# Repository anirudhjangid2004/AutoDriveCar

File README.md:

# AutoDriveCar
EDL 2025 project

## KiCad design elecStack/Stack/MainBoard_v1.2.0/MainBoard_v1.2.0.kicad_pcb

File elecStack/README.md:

### Electrical Architecture Information

The repo will contain the following

- Electrical board design
- Code for the low level microcontroller

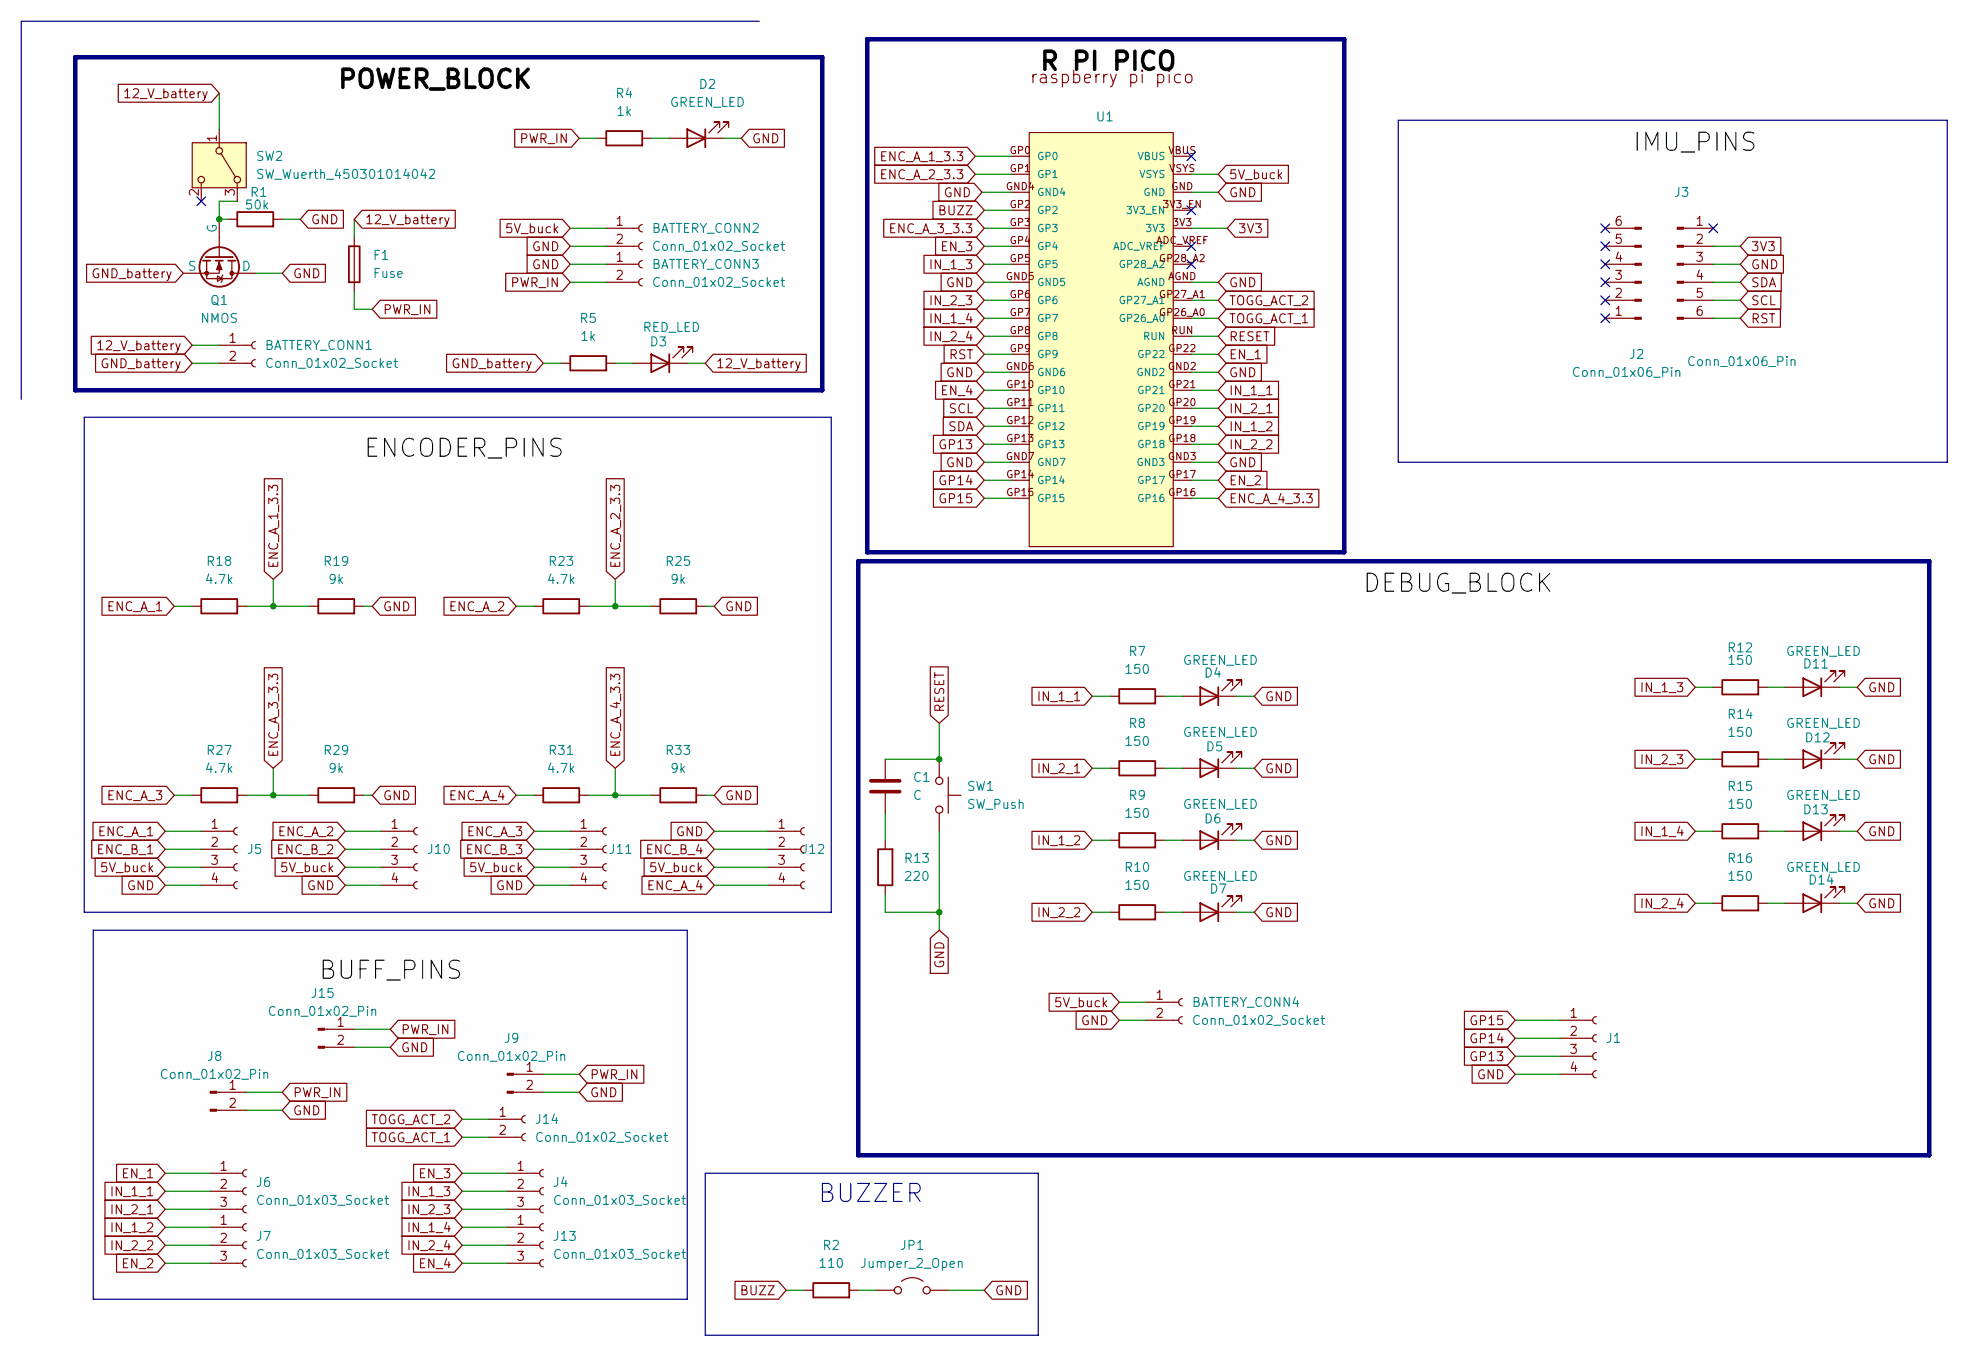
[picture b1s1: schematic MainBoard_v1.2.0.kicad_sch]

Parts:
BATTERY_CONN1, BATTERY_CONN2, BATTERY_CONN3, BATTERY_CONN4: Conn_01x02_Socket; TerminalBlock_Phoenix_MKDS-1,5-2-5.08_1x02_P5.08mm_Horizont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
C1: C; C_1210_3225Metric_Pad1.33x2.70mm_HandSolder
D2, D4, D5, D6, D7, D11, D12, D13, D14: GREEN_LED; LED_0805_2012Metric_Pad1.15x1.40mm_HandSolder
D3: RED_LED; LED_0805_2012Metric_Pad1.15x1.40mm_HandSolder
F1: Fuse; Fuse_Blade_Mini_directSolder
J1, J5, J10, J11, J12: Conn_01x04_Socket; JST_XH_B4B-XH-A_1x04_P2.50mm_Vertical
J2, J3: Conn_01x06_Pin; PinHeader_1x06_P2.54mm_Vertical
J4, J6, J7, J13: Conn_01x03_Socket; JST_XH_B3B-XH-A_1x03_P2.50mm_Vertical
J8, J9, J15: Conn_01x02_Pin; TerminalBlock_Phoenix_MKDS-1,5-2-5.08_1x02_P5.08mm_Horizont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
J14: Conn_01x02_Socket; JST_XH_B2B-XH-A_1x02_P2.50mm_Vertical
JP1: Jumper_2_Open; Buzzer_12x9.5RM7.6
Q1: NMOS; IRF540N
R1: 50k; R_0805_2012Metric_Pad1.20x1.40mm_HandSolder
R2: 110; R_0805_2012Metric_Pad1.20x1.40mm_HandSolder
R4, R5: 1k; R_0805_2012Metric_Pad1.20x1.40mm_HandSolder
R7, R8, R9, R10, R12, R14, R15, R16: 150; R_0805_2012Metric_Pad1.20x1.40mm_HandSolder
R13: 220; R_0805_2012Metric_Pad1.20x1.40mm_HandSolder
R18, R23, R27, R31: 4.7k; R_0805_2012Metric_Pad1.20x1.40mm_HandSolder
R19, R25, R29, R33: 9k; R_0805_2012Metric_Pad1.20x1.40mm_HandSolder
SW1: SW_Push; SW_PUSH_6mm_H5mm
SW2: SW_Wuerth_450301014042; SW_Slide-03_Wuerth-WS-SLTV_10x2.5x6.4_P2.54mm
U1: RASPBERRY_PI_PICO

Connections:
3V3: J3.2, U1.3V3
5V_buck: BATTERY_CONN2.1, BATTERY_CONN4.1, J5.3, J10.3, J11.3, J12.3, U1.VSYS
12_V_battery: BATTERY_CONN1.1, D3.1 (K), F1.1, SW2.1 (B)
BUZZ: R2.1, U1.GP2
ENC_A_1: J5.1, R18.1
ENC_A_1_3.3: R18.2, R19.1, U1.GP0
ENC_A_2: J10.1, R23.1
ENC_A_2_3.3: R23.2, R25.1, U1.GP1
ENC_A_3: J11.1, R27.1
ENC_A_3_3.3: R27.2, R29.1, U1.GP3
ENC_A_4: J12.4, R31.1
ENC_A_4_3.3: R31.2, R33.1, U1.GP16
ENC_B_1: J5.2
ENC_B_2: J10.2
ENC_B_3: J11.2
ENC_B_4: J12.2
EN_1: J6.1, U1.GP22
EN_2: J7.3, U1.GP17
EN_3: J4.1, U1.GP4
EN_4: J13.3, U1.GP10
GND: BATTERY_CONN2.2, BATTERY_CONN3.1, BATTERY_CONN4.2, D2.1 (K), D4.1 (K), D5.1 (K), D6.1 (K), D7.1 (K), D11.1 (K), D12.1 (K), D13.1 (K), D14.1 (K), J1.4, J3.3, J5.4, J8.2, J9.2, J10.4, J11.4, J12.1, J15.2, JP1.2 (B), Q1.1 (D), R1.2, R13.1, R19.2, R25.2, R29.2, R33.2, SW1.2, U1.AGND, U1.GND, U1.GND2, U1.GND3, U1.GND4, U1.GND5, U1.GND6, U1.GND7
GND_battery: BATTERY_CONN1.2, Q1.3 (S), R5.1
GP13: J1.3, U1.GP13
GP14: J1.2, U1.GP14
GP15: J1.1, U1.GP15
IN_1_1: J6.2, R7.1, U1.GP21
IN_1_2: J7.1, R9.1, U1.GP19
IN_1_3: J4.2, R12.1, U1.GP5
IN_1_4: J13.1, R15.1, U1.GP7
IN_2_1: J6.3, R8.1, U1.GP20
IN_2_2: J7.2, R10.1, U1.GP18
IN_2_3: J4.3, R14.1, U1.GP6
IN_2_4: J13.2, R16.1, U1.GP8
unnamed: C1.1, R13.2
unnamed: D2.2 (A), R4.2
unnamed: D3.2 (A), R5.2
unnamed: D4.2 (A), R7.2
unnamed: D5.2 (A), R8.2
unnamed: D6.2 (A), R9.2
unnamed: D7.2 (A), R10.2
unnamed: D11.2 (A), R12.2
unnamed: D12.2 (A), R14.2
unnamed: D13.2 (A), R15.2
unnamed: D14.2 (A), R16.2
unnamed: JP1.1 (A), R2.2
unnamed: Q1.2 (G), R1.1, SW2.3 (A)
PWR_IN: BATTERY_CONN3.2, F1.2, J8.1, J9.1, J15.1, R4.1
RESET: C1.2, SW1.1, U1.RUN
RST: J3.6, U1.GP9
SCL: J3.5, U1.GP11
SDA: J3.4, U1.GP12
TOGG_ACT_1: J14.2, U1.GP26_A0
TOGG_ACT_2: J14.1, U1.GP27_A1

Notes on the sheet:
BUZZER

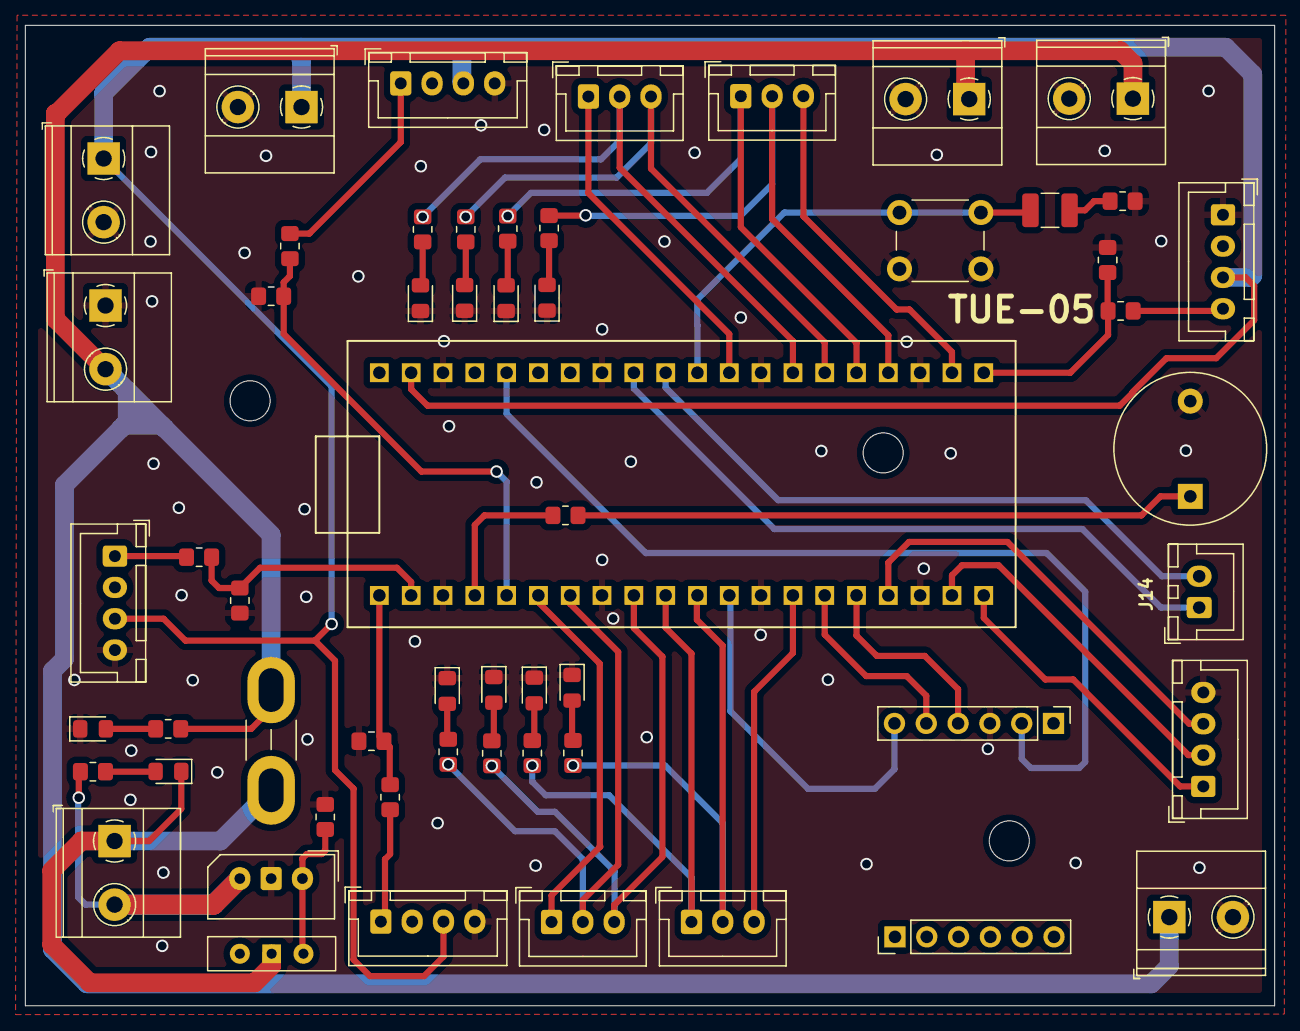
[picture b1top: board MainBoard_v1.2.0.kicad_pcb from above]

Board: 2 copper layers, 99.8 x 78.3 mm, 57 parts (0 on the bottom side), 49 nets.

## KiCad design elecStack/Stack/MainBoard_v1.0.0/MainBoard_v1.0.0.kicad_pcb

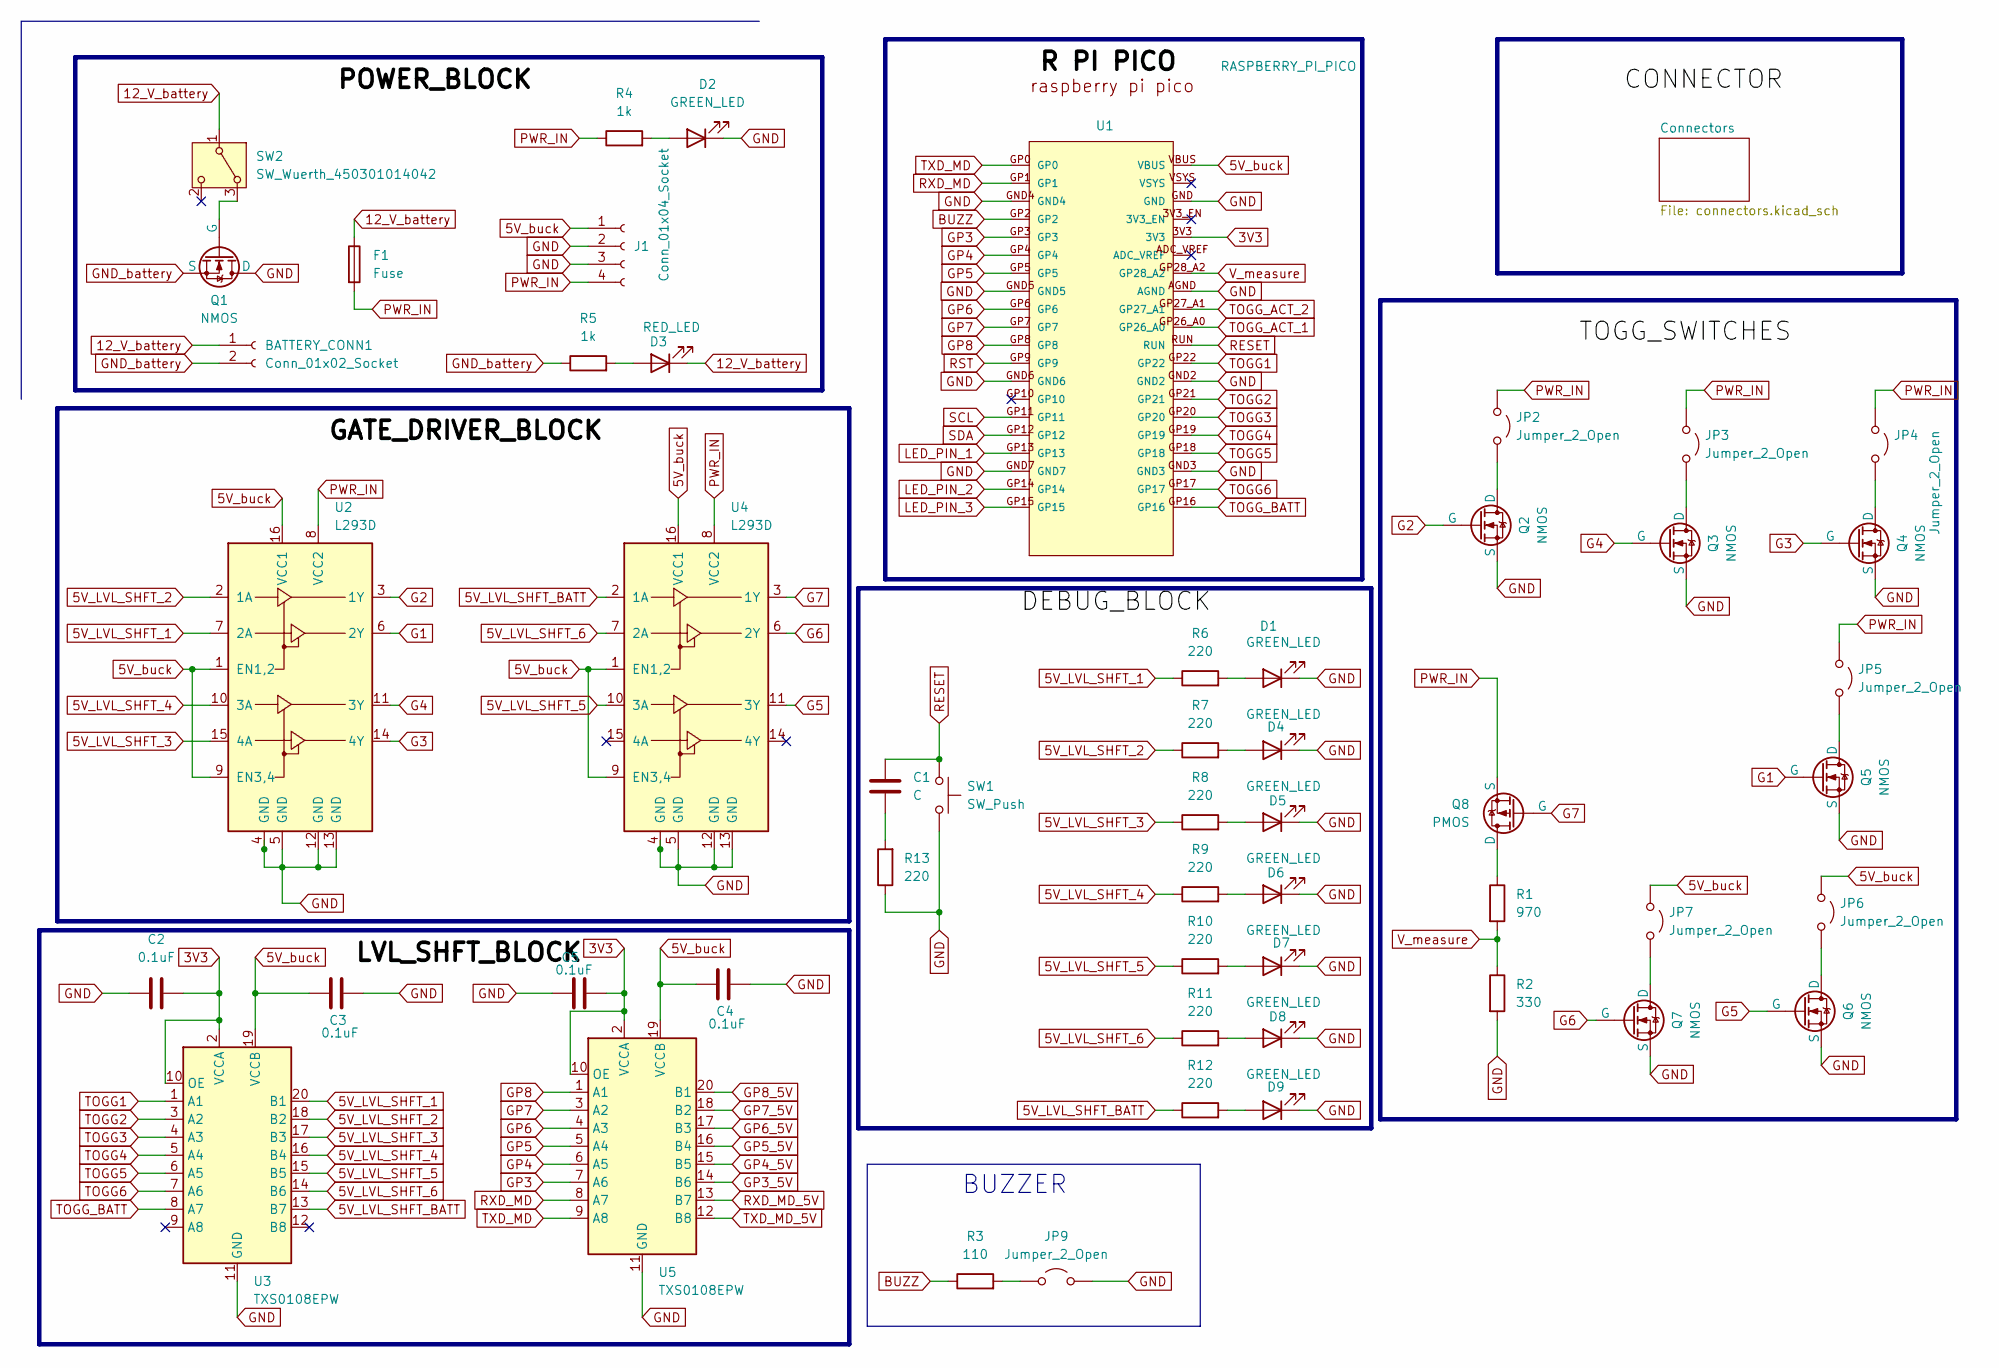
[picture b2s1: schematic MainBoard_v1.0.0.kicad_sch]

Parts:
BATTERY_CONN1: Conn_01x02_Socket; PhoenixContact_MSTBA_2,5_2-G-5,08_1x02_P5.08mm_Horizontal
C1: C; C_1210_3225Metric_Pad1.33x2.70mm_HandSolder
C2, C3, C4, C5: 0.1uF; C_1210_3225Metric_Pad1.33x2.70mm_HandSolder
D1, D2, D4, D5, D6, D7, D8, D9: GREEN_LED; LED_0805_2012Metric_Pad1.15x1.40mm_HandSolder
D3: RED_LED; LED_0805_2012Metric_Pad1.15x1.40mm_HandSolder
F1: Fuse; Fuse_Blade_Mini_directSolder
J1: Conn_01x04_Socket; PhoenixContact_MSTBA_2,5_4-G_1x04_P5.00mm_Horizontal
JP2, JP3, JP4, JP5, JP6, JP7: Jumper_2_Open; PhoenixContact_MSTBA_2,5_2-G_1x02_P5.00mm_Horizontal
JP9: Jumper_2_Open; Buzzer_12x9.5RM7.6
Q1, Q2, Q3, Q4, Q5, Q6, Q7: NMOS; Molex_SPOX_5267-03A_1x03_P2.50mm_Vertical
Q8: PMOS; Molex_SPOX_5267-03A_1x03_P2.50mm_Vertical
R1: 970; R_0805_2012Metric_Pad1.20x1.40mm_HandSolder
R2: 330; R_0805_2012Metric_Pad1.20x1.40mm_HandSolder
R3: 110; R_0805_2012Metric_Pad1.20x1.40mm_HandSolder
R4, R5: 1k; R_0805_2012Metric_Pad1.20x1.40mm_HandSolder
R6, R7, R8, R9, R10, R11, R12, R13: 220; R_0805_2012Metric_Pad1.20x1.40mm_HandSolder
SW1: SW_Push; SW_PUSH_6mm_H5mm
SW2: SW_Wuerth_450301014042; SW_Slide-03_Wuerth-WS-SLTV_10x2.5x6.4_P2.54mm
U1: RASPBERRY_PI_PICO
U2, U4: L293D; DIP-16_W7.62mm
U3, U5: TXS0108EPW; PinHeader_1x10_P2.54mm_Vertical_1

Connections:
3V3: C2.2, C5.1, U1.3V3, U3.2 (VCCA), U3.10 (OE), U5.2 (VCCA), U5.10 (OE); also elsewhere on the board
5V_LVL_SHFT_1: R6.1, U2.7 (2A), U3.20 (B1)
5V_LVL_SHFT_2: R7.1, U2.2 (1A), U3.18 (B2)
5V_LVL_SHFT_3: R8.1, U2.15 (4A), U3.17 (B3)
5V_LVL_SHFT_4: R9.1, U2.10 (3A), U3.16 (B4)
5V_LVL_SHFT_5: R10.1, U3.15 (B5), U4.10 (3A)
5V_LVL_SHFT_6: R11.1, U3.14 (B6), U4.7 (2A)
5V_LVL_SHFT_BATT: R12.1, U3.13 (B7), U4.2 (1A)
5V_buck: C3.1, C4.1, J1.1, JP6.1 (A), JP7.1 (A), U1.VBUS, U2.1 (EN1,2), U2.9 (EN3,4), U2.16 (VCC1), U3.19 (VCCB), U4.1 (EN1,2), U4.9 (EN3,4), U4.16 (VCC1), U5.19 (VCCB); also elsewhere on the board
12_V_battery: BATTERY_CONN1.1, D3.1 (K), F1.1, SW2.1 (B)
BUZZ: R3.1, U1.GP2
G1: Q5.2 (G), U2.6 (2Y)
G2: Q2.2 (G), U2.3 (1Y)
G3: Q4.2 (G), U2.14 (4Y)
G4: Q3.2 (G), U2.11 (3Y)
G5: Q6.2 (G), U4.11 (3Y)
G6: Q7.2 (G), U4.6 (2Y)
G7: Q8.2 (G), U4.3 (1Y)
GND: C2.1, C3.2, C4.2, C5.2, D1.1 (K), D2.1 (K), D4.1 (K), D5.1 (K), D6.1 (K), D7.1 (K), D8.1 (K), D9.1 (K), J1.2, J1.3, JP9.2 (B), Q1.1 (D), Q2.3 (S), Q3.3 (S), Q4.3 (S), Q5.3 (S), Q6.3 (S), Q7.3 (S), R2.2, R13.1, SW1.2, U1.AGND, U1.GND, U1.GND2, U1.GND3, U1.GND4, U1.GND5, U1.GND6, U1.GND7, U2.4 (GND), U2.5 (GND), U2.12 (GND), U2.13 (GND), U3.11 (GND), U4.4 (GND), U4.5 (GND), U4.12 (GND), U4.13 (GND), U5.11 (GND); also elsewhere on the board
GND_battery: BATTERY_CONN1.2, Q1.3 (S), R5.1
GP3: U1.GP3, U5.7 (A6)
GP3_5V: U5.14 (B6); also elsewhere on the board
GP4: U1.GP4, U5.6 (A5)
GP4_5V: U5.15 (B5); also elsewhere on the board
GP5: U1.GP5, U5.5 (A4)
GP5_5V: U5.16 (B4); also elsewhere on the board
GP6: U1.GP6, U5.4 (A3)
GP6_5V: U5.17 (B3); also elsewhere on the board
GP7: U1.GP7, U5.3 (A2)
GP7_5V: U5.18 (B2); also elsewhere on the board
GP8: U1.GP8, U5.1 (A1)
GP8_5V: U5.20 (B1); also elsewhere on the board
LED_PIN_1: U1.GP13; also elsewhere on the board
LED_PIN_2: U1.GP14; also elsewhere on the board
LED_PIN_3: U1.GP15; also elsewhere on the board
unnamed: C1.1, R13.2
unnamed: D1.2 (A), R6.2
unnamed: D2.2 (A), R4.2
unnamed: D3.2 (A), R5.2
unnamed: D4.2 (A), R7.2
unnamed: D5.2 (A), R8.2
unnamed: D6.2 (A), R9.2
unnamed: D7.2 (A), R10.2
unnamed: D8.2 (A), R11.2
unnamed: D9.2 (A), R12.2
unnamed: JP2.2 (B), Q2.1 (D)
unnamed: JP3.2 (B), Q3.1 (D)
unnamed: JP4.2 (B), Q4.1 (D)
unnamed: JP5.2 (B), Q5.1 (D)
unnamed: JP6.2 (B), Q6.1 (D)
unnamed: JP7.2 (B), Q7.1 (D)
unnamed: JP9.1 (A), R3.2
unnamed: Q1.2 (G), SW2.3 (A)
unnamed: Q8.1 (D), R1.1
PWR_IN: F1.2, J1.4, JP2.1 (A), JP3.1 (A), JP4.1 (A), JP5.1 (A), Q8.3 (S), R4.1, U2.8 (VCC2), U4.8 (VCC2); also elsewhere on the board
RESET: C1.2, SW1.1, U1.RUN
RST: U1.GP9; also elsewhere on the board
RXD_MD: U1.GP1, U5.8 (A7)
RXD_MD_5V: U5.13 (B7); also elsewhere on the board
SCL: U1.GP11; also elsewhere on the board
SDA: U1.GP12; also elsewhere on the board
TOGG1: U1.GP22, U3.1 (A1)
TOGG2: U1.GP21, U3.3 (A2)
TOGG3: U1.GP20, U3.4 (A3)
TOGG4: U1.GP19, U3.5 (A4)
TOGG5: U1.GP18, U3.6 (A5)
TOGG6: U1.GP17, U3.7 (A6)
TOGG_ACT_1: U1.GP26_A0; also elsewhere on the board
TOGG_ACT_2: U1.GP27_A1; also elsewhere on the board
TOGG_BATT: U1.GP16, U3.8 (A7)
TXD_MD: U1.GP0, U5.9 (A8)
TXD_MD_5V: U5.12 (B8); also elsewhere on the board
V_measure: R1.2, R2.1, U1.GP28_A2

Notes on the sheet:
BUZZER

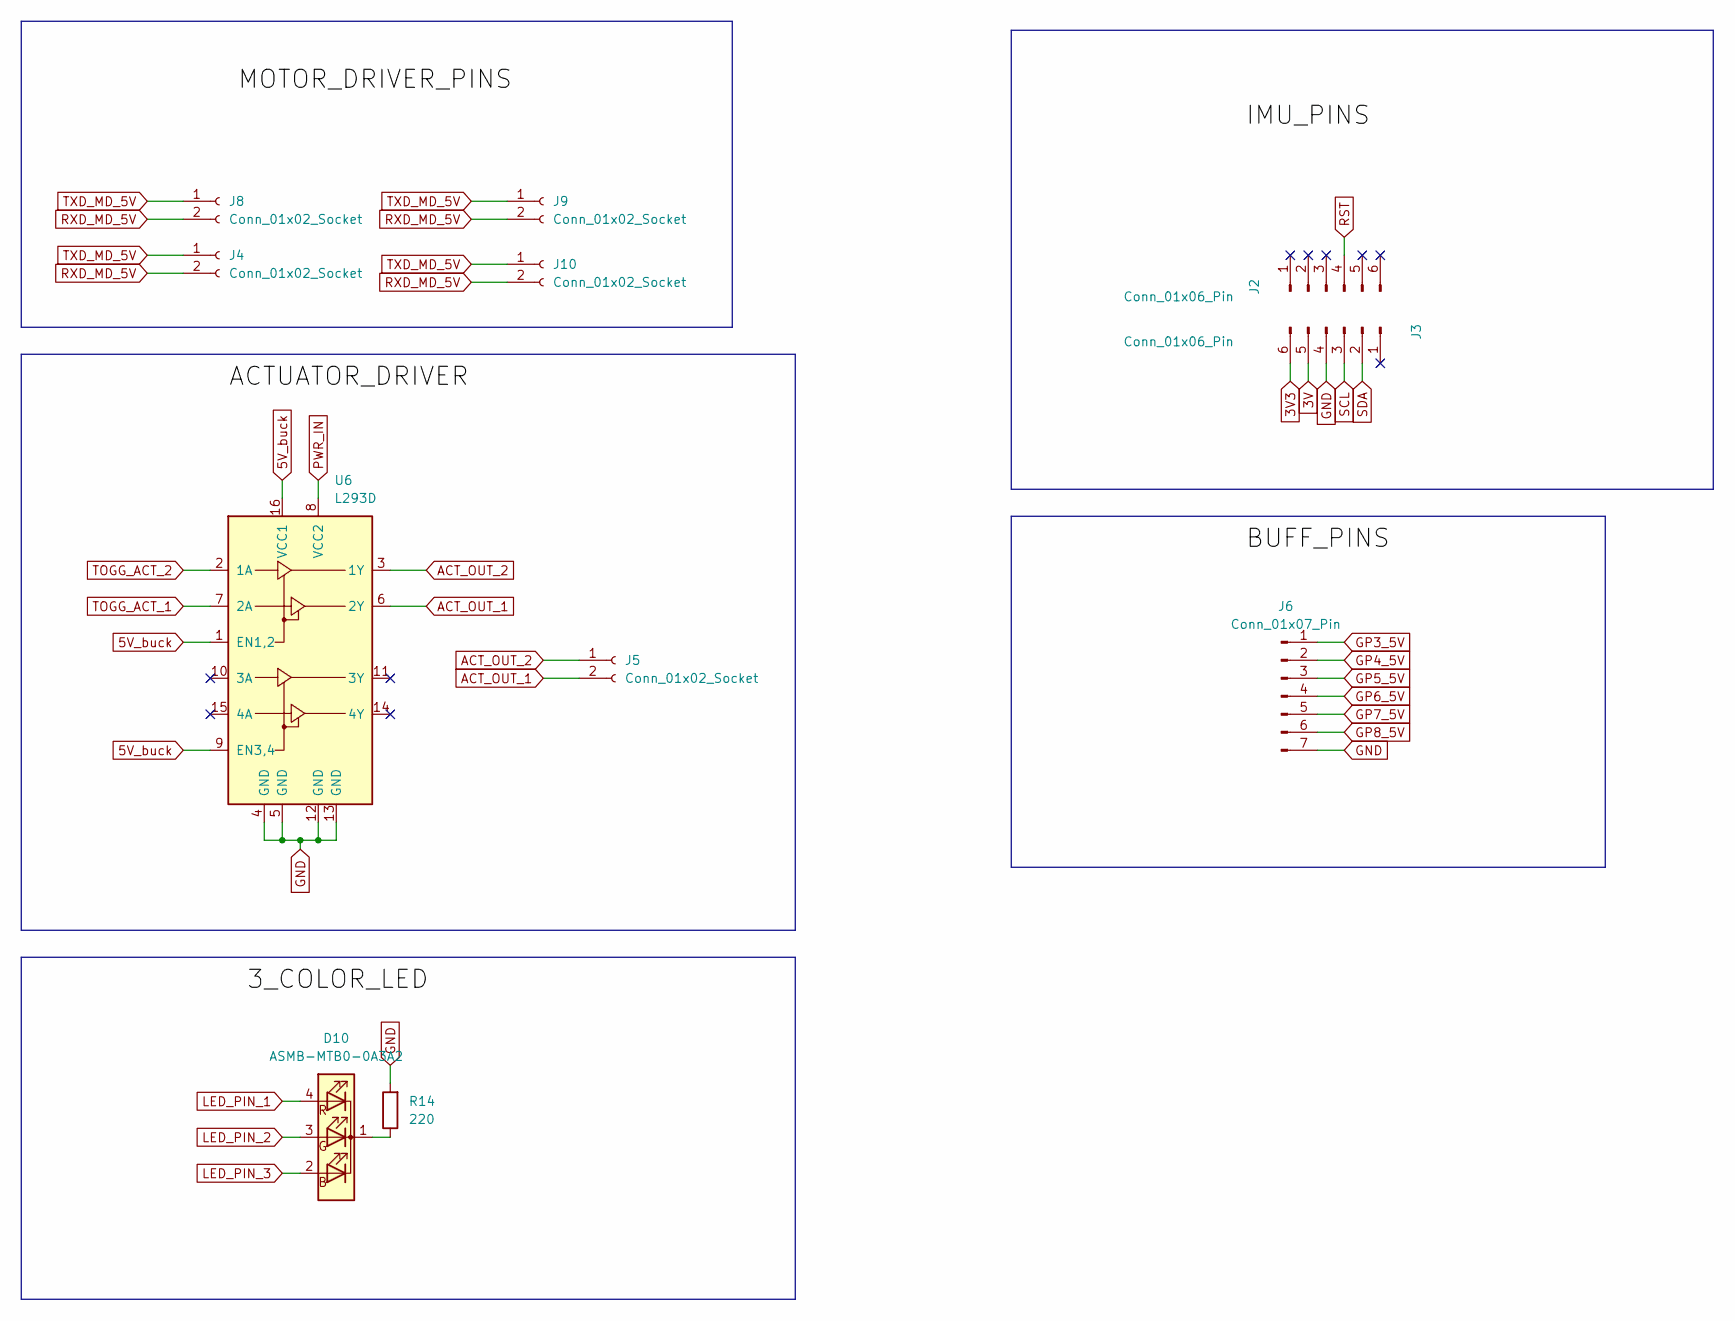
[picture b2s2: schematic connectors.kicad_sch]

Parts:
D10: ASMB-MTB0-0A3A2; LED_D5.0mm-4_RGB
J2, J3: Conn_01x06_Pin; PinHeader_1x06_P2.54mm_Vertical
J4, J5, J8, J9, J10: Conn_01x02_Socket; PhoenixContact_MSTBA_2,5_2-G_1x02_P5.00mm_Horizontal
J6: Conn_01x07_Pin; PinHeader_1x07_P2.54mm_Vertical
R14: 220; R_0805_2012Metric_Pad1.20x1.40mm_HandSolder
U6: L293D; DIP-16_W7.62mm

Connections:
3V: J3.5
3V3: J3.6; also elsewhere on the board
5V_buck: U6.1 (EN1,2), U6.9 (EN3,4), U6.16 (VCC1); also elsewhere on the board
ACT_OUT_1: J5.2, U6.6 (2Y)
ACT_OUT_2: J5.1, U6.3 (1Y)
GND: J3.4, J6.7, J8.3, J9.3, J10.3, R14.2, U6.4 (GND), U6.5 (GND), U6.12 (GND), U6.13 (GND); also elsewhere on the board
GP3_5V: J6.1; also elsewhere on the board
GP4_5V: J6.2; also elsewhere on the board
GP5_5V: J6.3; also elsewhere on the board
GP6_5V: J6.4; also elsewhere on the board
GP7_5V: J6.5; also elsewhere on the board
GP8_5V: J6.6; also elsewhere on the board
LED_PIN_1: D10.4 (RK); also elsewhere on the board
LED_PIN_2: D10.3 (GK); also elsewhere on the board
LED_PIN_3: D10.2 (BK); also elsewhere on the board
unnamed: D10.1 (A), R14.1
PWR_IN: U6.8 (VCC2); also elsewhere on the board
RST: J2.4; also elsewhere on the board
RXD_MD_5V: J4.2, J8.2, J9.2, J10.2; also elsewhere on the board
SCL: J3.3; also elsewhere on the board
SDA: J3.2; also elsewhere on the board
TOGG_ACT_1: U6.7 (2A); also elsewhere on the board
TOGG_ACT_2: U6.2 (1A); also elsewhere on the board
TXD_MD_5V: J4.1, J8.1, J9.1, J10.1; also elsewhere on the board

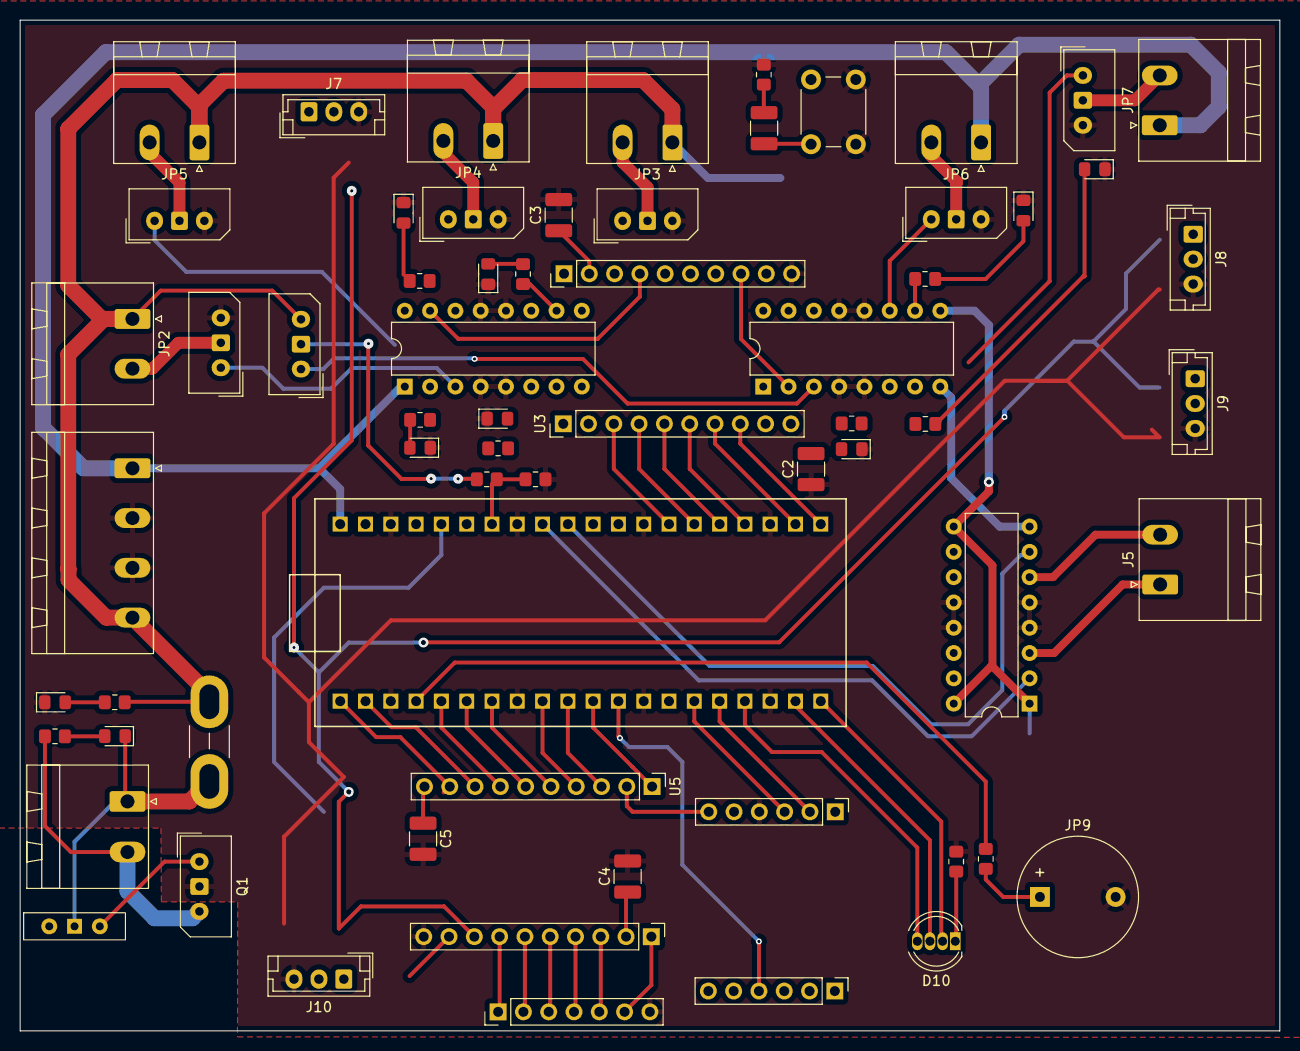
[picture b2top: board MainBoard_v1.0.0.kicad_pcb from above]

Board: 2 copper layers, 126.5 x 101.5 mm, 63 parts (0 on the bottom side), 76 nets.

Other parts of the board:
J7: Conn_01x03_Socket; JST_EH_B3B-EH-A_1x03_P2.50mm_Vertical

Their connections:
GND: J7.3; also elsewhere on the board
RXD_MD_5V: J7.2; also elsewhere on the board
TXD_MD_5V: J7.1; also elsewhere on the board

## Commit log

2025-02-04 Creating the repositories
2025-02-06 Adding intro files
2025-02-08 Adding Pico Footprint
2025-02-08 Rename report.md to README.md
2025-02-08 Adding motor driver files
2025-02-08 Ported the codes for Pico
2025-02-11 Adding elec stack files
2025-02-11 Changes in motor driver
2025-02-14 Iteration_1 of PCB
2025-02-15 Updated version 1
2025-02-16 Make changes indicated in the schematic
2025-02-16 added ros2 ws
2025-02-16 IMU_connected
2025-02-16 Added RMCS-2303 updated datasheet
2025-02-18 Addding stack v1_2
2025-02-18 tried slam_toolbox, small changes in rsp launch file
2025-02-18 added basic aruco detection codes
2025-02-18 Environment for Code dev ready in Stackv1_2_0
2025-02-19 added twist_mux
2025-02-25 Adding changes of elec stack
2025-03-03 updated placements
2025-03-04 Routing done
2025-03-05 Made basic changes in code
2025-03-05 Adding the IMU code files
2025-03-11 updated_11_march
2025-03-17 Added code for Encoder Data Readding
2025-03-19 Adding the corrected encoder code with all other files
2025-03-20 Completed USB Driver, still left to allocate pwm in main code
2025-03-20 Main files completed with PWM Distribution
2025-03-21 Added and modified USB Driver
2025-03-22 version_1.2.0 layout
2025-03-22 version 1.2.0 layout done
2025-03-23 Motor commands working fine and complete, encoder integration left
2025-03-29 final_PCB
2025-03-31 Adding nano driver for usb
2025-04-01 Everything working
